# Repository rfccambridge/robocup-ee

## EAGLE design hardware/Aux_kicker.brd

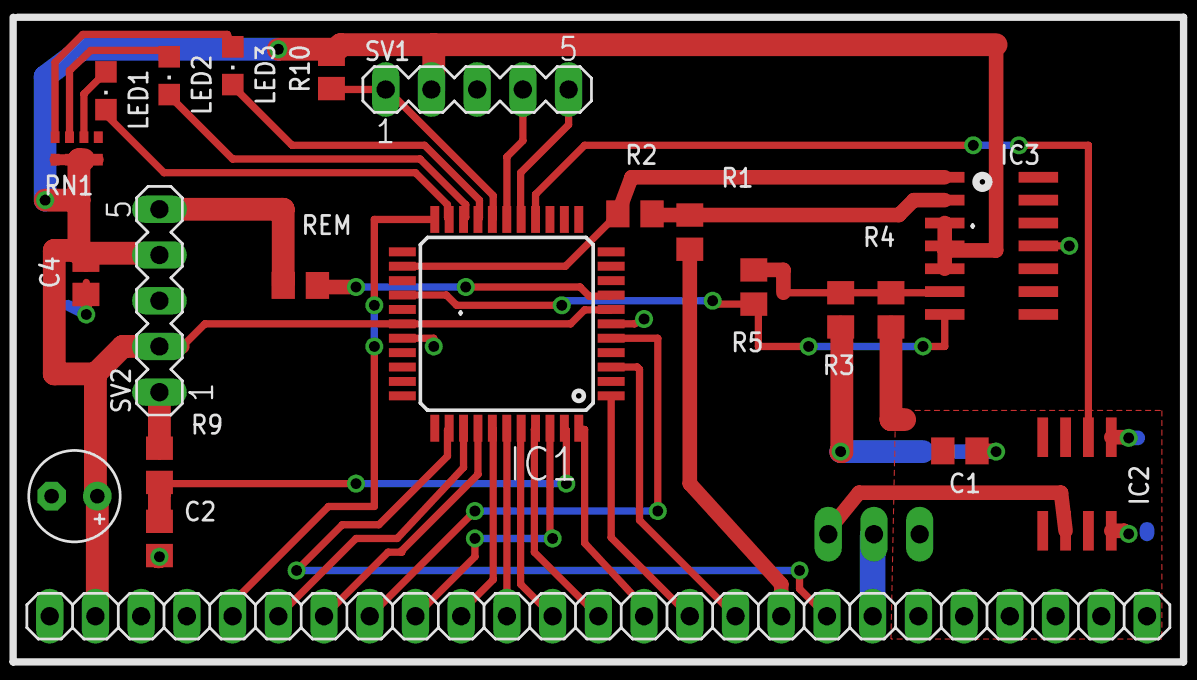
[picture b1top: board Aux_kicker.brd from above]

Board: 2 copper layers, 23 parts (1 on the bottom side), 38 nets.

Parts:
C1, C2, C4: 1uF; C0805
C14: 100uF; E2,5-5
IC1: TQFP44@1
IC2: MIC4429M; SO-08
IC3: LM324D; SO14
JP2: 1X25
LED1, LED2, LED3: CHIPLED_0805
Q1: IRF520; TO220BV
R1: 1M; R0805
R2: 8.45k; R0805
R3: 10k; R0805
R4: 20k; R0805
R5: 7.15k; R0805
R9: 110; R0805
R10: 10K; R0805
REM: 50k; R0805
RN1: 220; 0603-ARC
SV1, SV2: MA05-1

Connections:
+5V: C4.1, C14.+, IC1.7, IC1.28, IC3.3, IC3.5, JP2.2, R10.2, RN1.1, RN1.2, RN1.3, RN1.4, SV1.2, SV2.2, SV2.4
+12V: C1.1, IC2.1, IC2.8, JP2.20, JP2.21, JP2.22, R3.1
BATTV: IC1.26, IC3.7, R5.1
BBEMVO: REM.2, SV2.5
BBFREQOUT: IC1.8, REM.1
BBOUT: C2.1, IC1.43, R9.2
BBTRVO: R9.1, SV2.1
BOTID0: IC1.38, JP2.10
BOTID1: IC1.39, JP2.11
BOTID2: IC1.40, JP2.12
BOTID3: IC1.41, JP2.13
CAP+: JP2.17, R1.2
CAPV: IC1.24, IC3.1, R2.1
CHARGE: IC1.5, JP2.8
CHIPKICK: IC1.36, JP2.6
DISCHARGE: IC1.35, JP2.18
DONE: IC1.42, JP2.9
DRIB: JP2.19, Q1.D
FWDKICK: IC1.37, JP2.7
GND: C2.2, C4.2, C14.-, IC1.6, IC1.29, JP2.1, SV1.3, SV2.3
LED1: IC1.21, LED1.C
LED2: IC1.20, LED2.C
LED3: IC1.19, LED3.C
LEDF1: IC1.22, JP2.5
N30: IC1.15, IC2.2
unnamed: LED3.A, RN1.8
unnamed: LED2.A, RN1.7
unnamed: LED1.A, RN1.6
unnamed: IC3.2, R1.1, R2.2
unnamed: IC2.6, Q1.G
unnamed: IC3.6, R3.2, R4.1, R5.2
unnamed: IC1.18, R10.1, SV1.1
unnamed: IC1.17, SV1.4
unnamed: IC1.16, SV1.5
PE: C1.2, IC2.4, IC2.5, JP2.23, JP2.24, JP2.25, Q1.S, R4.2
RX: IC1.1, JP2.15
TX: IC1.44, JP2.14
TXEN: IC1.3, JP2.16

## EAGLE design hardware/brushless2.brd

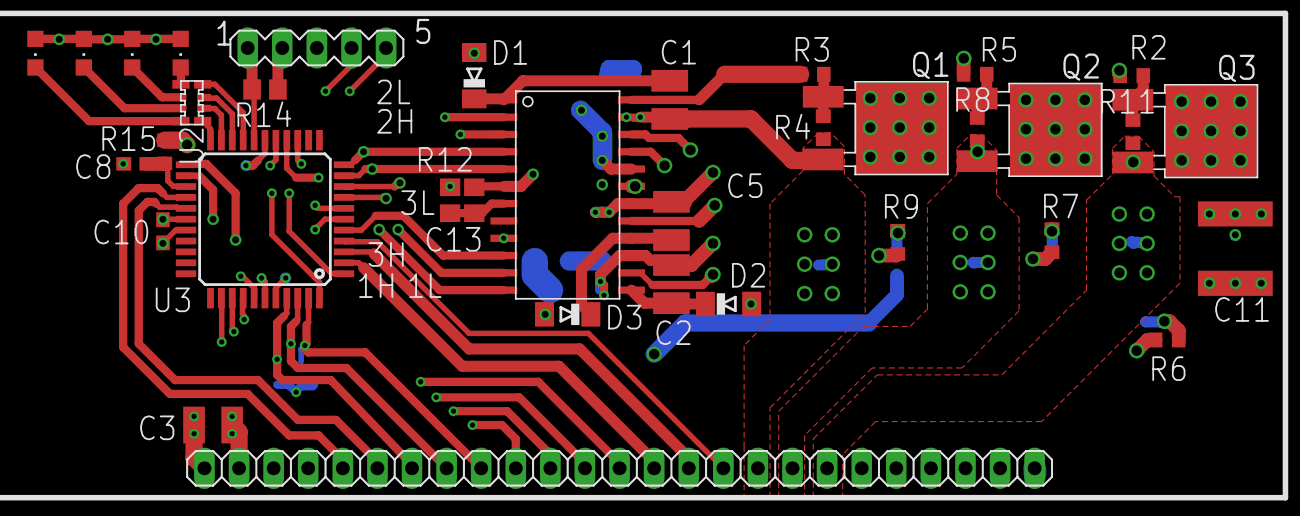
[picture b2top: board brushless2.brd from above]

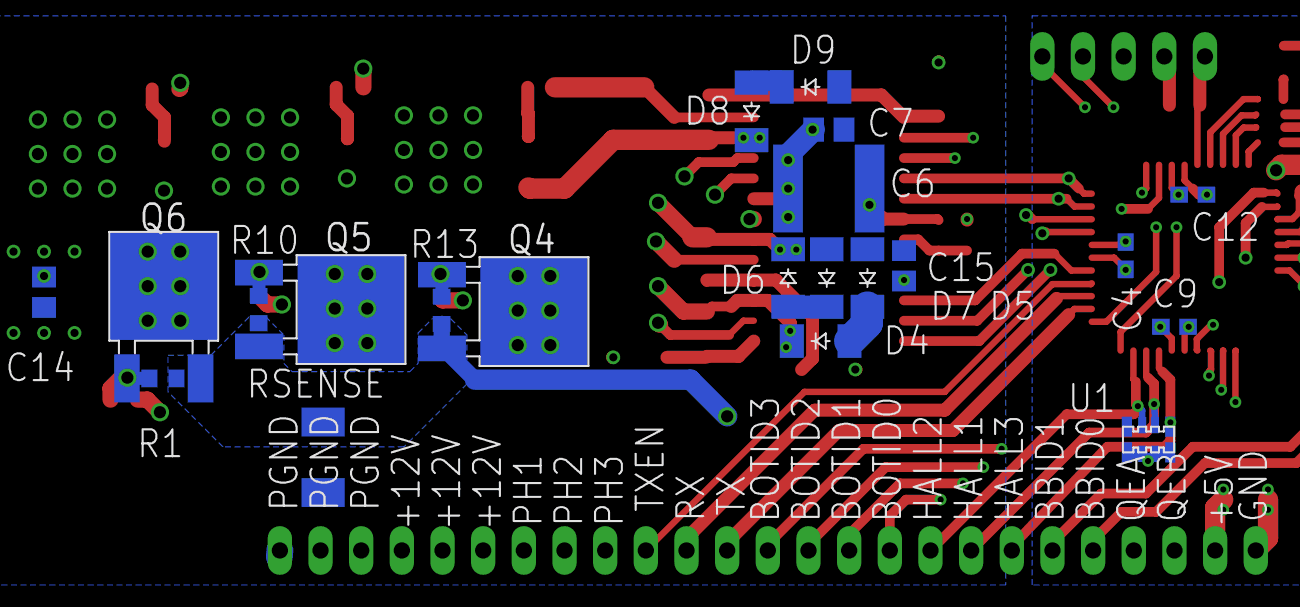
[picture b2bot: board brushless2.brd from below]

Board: 4 copper layers, 56 parts (21 on the bottom side), 61 nets.

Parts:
C1, C2, C5: 1u; C1210
C3: 10u; C1210
C4, C8, C9, C10, C12: .1u; C0603
C6, C11: 100u; C2220K
C7, C13, C14: 0.1u; C0805
C15: 50p; C0805
D1, D2, D3: MINIMELF
D4, D5, D6, D7, D8, D9: CGRM4001-G; SOD-123_MINI-SMA
ICSP1: MA05-1
JP1: 1X25
LED1, LED2, LED3, LED4: CHIPLED_0805
Q1, Q2, Q3, Q4, Q5, Q6: DPAK
R1, R4, R8, R10, R11, R13: 100k; R0603
R2, R3, R5, R6, R7, R9: 5; R0603
R12: 50k; R0805
R14: 10k; R0805
R15: 1k; R0603
RSENSE: 47m; R2010
U1: 10K; 0603X4
U2: 220; 0603X4
U3: DSPIC30F4011; TQFP44
U4: HIP4086

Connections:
+5V: C3.1, C4.1, C9.1, C10.1, C12.1, ICSP1.2, JP1.2, LED1.A, LED2.A, LED3.A, LED4.A, R14.1, U1.P$3, U1.P$4, U1.P$6, U1.P$8, U3.7, U3.17, U3.28, U3.40
+12V: C6.1, C7.1, C11.1, C14.1, D1.A, D2.A, D3.A, JP1.20, JP1.21, JP1.22, Q1.DRAIN, Q2.DRAIN, Q3.DRAIN, R12.1, U4.20
BBID0: JP1.5, U3.26
BBID1: JP1.6, U3.27
BOTID0: JP1.10, U3.35
BOTID1: JP1.11, U3.36
BOTID2: JP1.12, U3.37
BOTID3: JP1.13, U3.38
GND: C3.2, C4.2, C8.2, C9.2, C10.2, C12.2, ICSP1.3, JP1.1, U3.6, U3.16, U3.29, U3.39
H1: U3.14, U4.12
H2: U3.10, U4.5
H3: U3.8, U4.2
HALL1: JP1.8, U1.P$1, U3.42
HALL2: JP1.9, U1.P$2, U3.43
HALL3: JP1.7, U1.P$5, U3.41
L1: U3.15, U4.11
L2: U3.11, U4.4
L3: U3.9, U4.3
LED1: U2.P$5, U3.22
LED2: U2.P$1, U3.21
LED3: U2.P$2, U3.20
LED4: U2.P$7, U3.19
MCLR: ICSP1.1, R14.2, U3.18
unnamed: C1.1, D1.C, U4.1
unnamed: LED1.C, U2.P$6
unnamed: LED2.C, U2.P$4
unnamed: Q1.GATE, R3.1, R4.2
unnamed: R3.2, U4.24
unnamed: R9.2, U4.22
unnamed: LED3.C, U2.P$3
unnamed: R7.2, U4.21
unnamed: D4.A, D5.C
unnamed: Q5.GATE, R7.1, R10.2
unnamed: Q2.GATE, R5.1, R8.2
unnamed: R6.2, U4.19
unnamed: Q4.GATE, R9.1, R13.2
unnamed: C2.1, D2.C, U4.13
unnamed: R2.2, U4.14
unnamed: R5.2, U4.17
unnamed: Q3.GATE, R2.1, R11.2
unnamed: C5.1, D3.C, U4.16
unnamed: C15.1, U4.9
unnamed: C13.1, R12.2, U4.7
unnamed: D6.A, D7.C
unnamed: D8.A, D9.C
unnamed: LED4.C, U2.P$8
unnamed: Q6.GATE, R1.2, R6.1
PE: C6.2, C7.2, C11.2, C13.2, C14.2, C15.2, D5.A, D7.A, D9.A, JP1.23, JP1.24, JP1.25, RSENSE.1, U4.6
PGC: ICSP1.5, U3.1
PGD: ICSP1.4, U3.44
PH1: C2.2, D4.C, JP1.19, Q3.SOURCE, Q6.DRAIN, R11.1, U4.15
PH2: C5.2, D6.C, JP1.18, Q2.SOURCE, Q5.DRAIN, R8.1, U4.18
PH3: C1.2, D8.C, JP1.17, Q1.SOURCE, Q4.DRAIN, R4.1, U4.23
PWMDIS: U3.5, U4.10
QEA: JP1.4, U3.23
QEB: JP1.3, U3.24
RX: JP1.15, U3.3
SENSE: C8.1, R15.2, U3.25
TX: JP1.14, U3.2
TXEN: JP1.16, U3.4
VSO: Q4.SOURCE, Q5.SOURCE, Q6.SOURCE, R1.1, R10.1, R13.1, R15.1, RSENSE.2
